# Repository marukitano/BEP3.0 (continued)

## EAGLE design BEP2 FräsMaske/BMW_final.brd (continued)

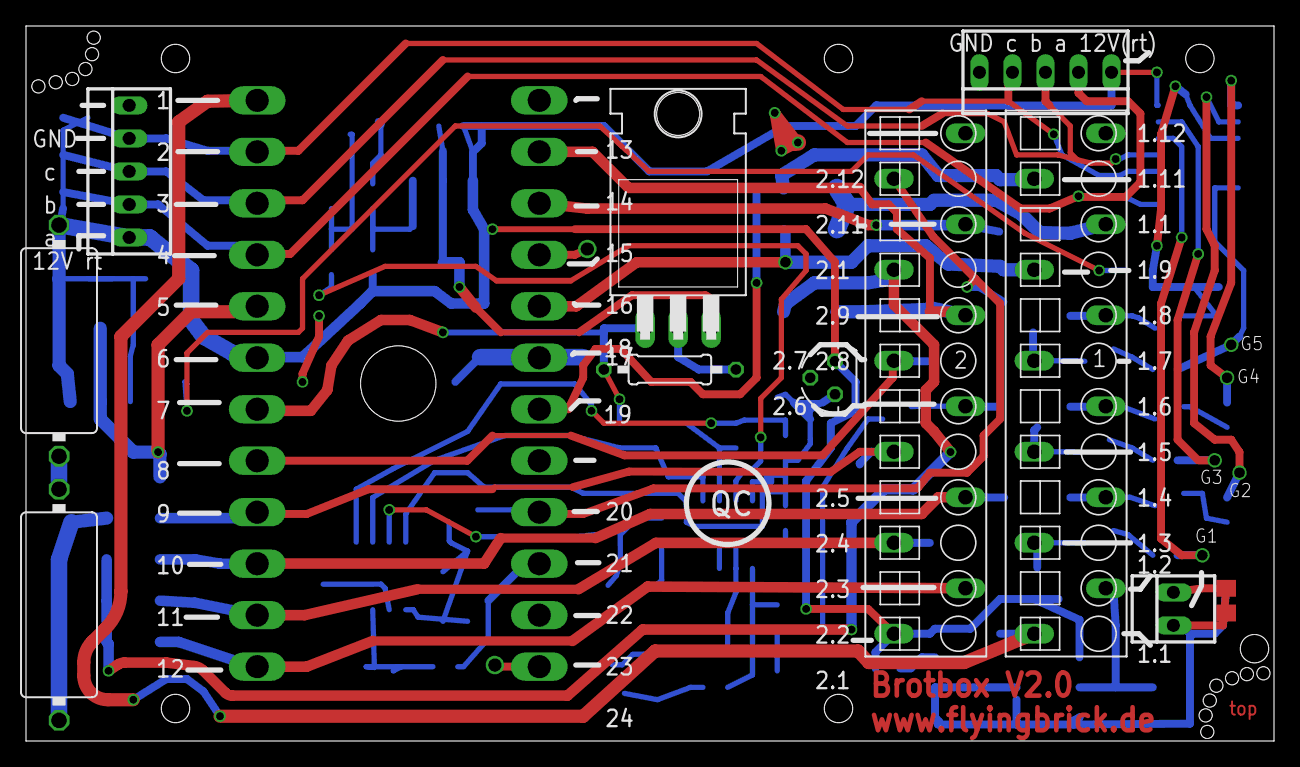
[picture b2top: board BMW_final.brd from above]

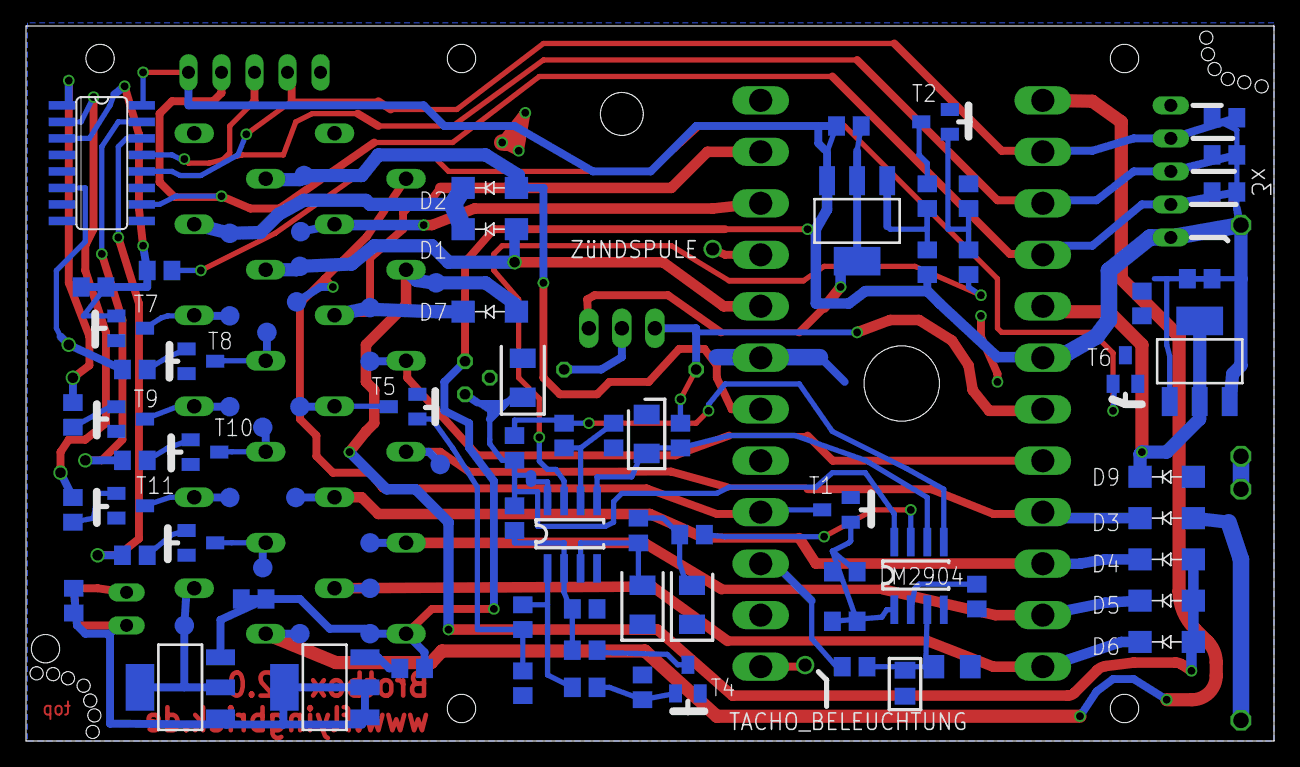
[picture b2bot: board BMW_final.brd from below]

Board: 2 copper layers, 96.0 x 55.0 mm, 105 parts (93 on the bottom side), 73 nets.

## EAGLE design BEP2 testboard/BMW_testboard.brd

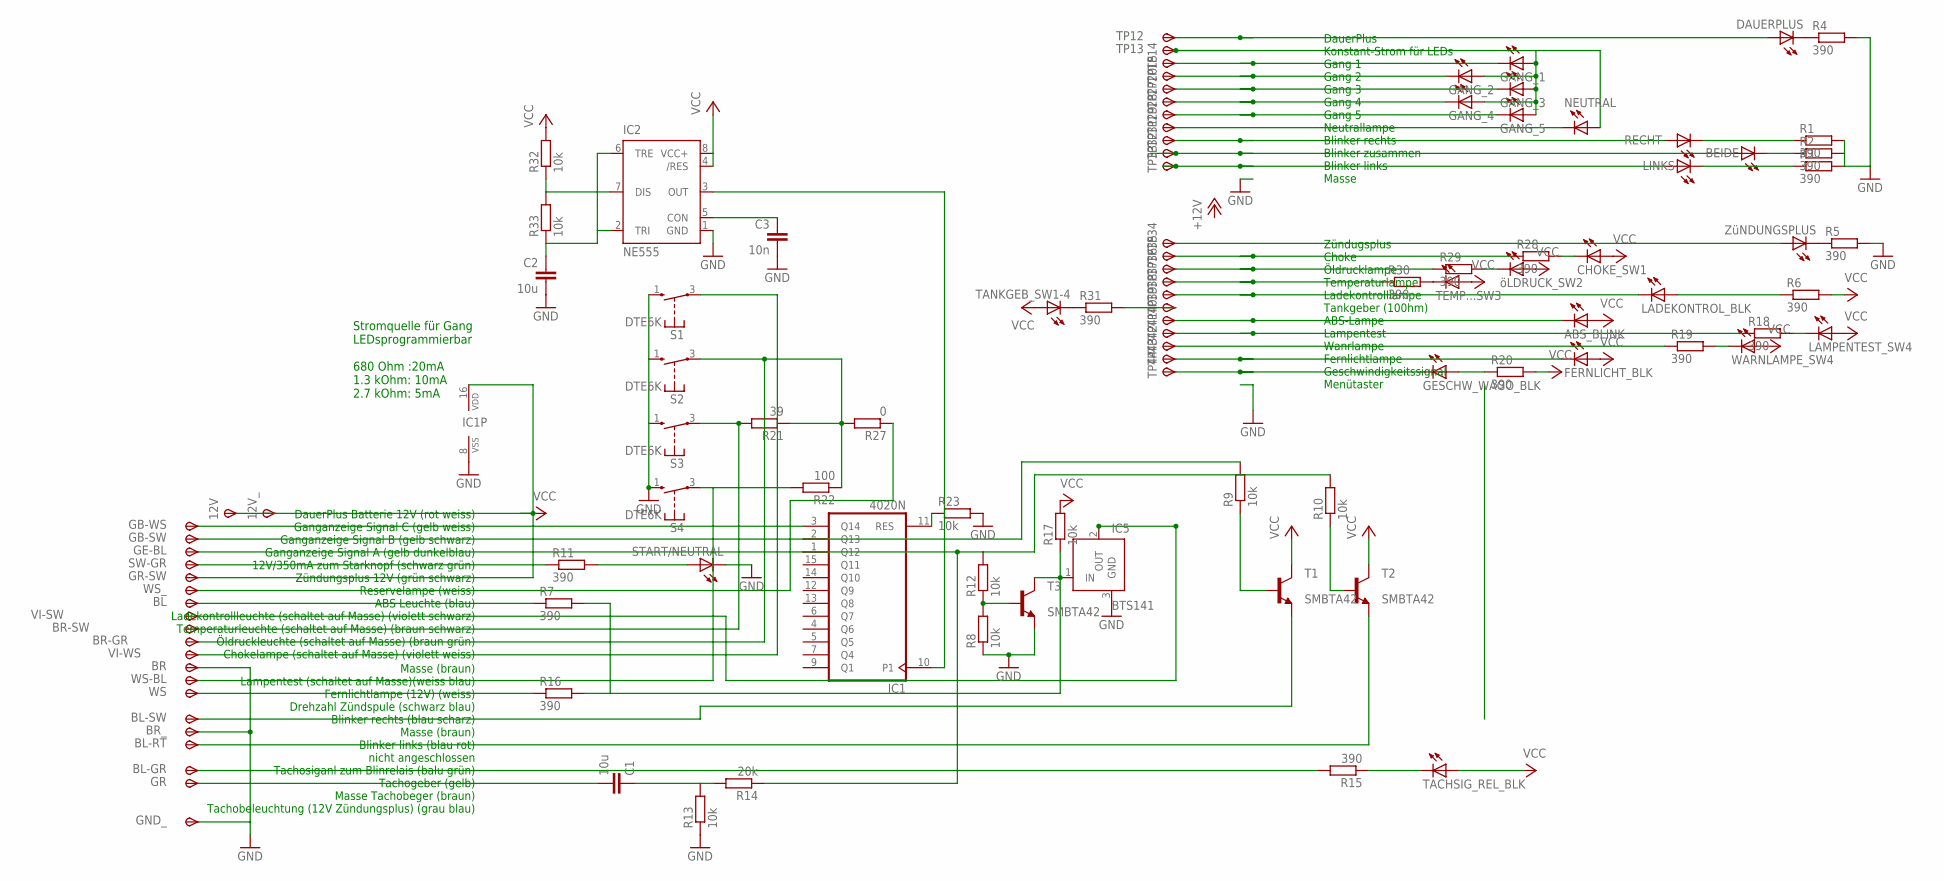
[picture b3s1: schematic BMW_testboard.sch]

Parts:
12V, 12V_: TPSPAD1-1.5MM; P1-13
ABS_BLINK: TLLY4400; LED3MM
BEIDE: TLLY4400; LED3MM
BL: TPSPAD1-1.5MM; P1-13
BL-GR: TPSPAD1-1.5MM; P1-13
BL-RT: TPSPAD1-1.5MM; P1-13
BL-SW: TPSPAD1-1.5MM; P1-13
BR: TPSPAD1-1.5MM; P1-13
BR-GR: TPSPAD1-1.5MM; P1-13
BR-SW: TPSPAD1-1.5MM; P1-13
BR_: TPSPAD1-1.5MM; P1-13
C1, C2: 10u; C025-024X044
C3: 10n; C025-024X044
CHOKE_SW1: TLLY4400; LED3MM
DAUERPLUS: TLLY4400; LED3MM
FERNLICHT_BLK: TLLY4400; LED3MM
GANG_1, GANG_2, GANG_3, GANG_4, GANG_5: TLLY4400; LED3MM
GB-SW: TPSPAD1-1.5MM; P1-13
GB-WS: TPSPAD1-1.5MM; P1-13
GE-BL: TPSPAD1-1.5MM; P1-13
GESCHW_WAGO_BLK: TLLY4400; LED3MM
GND_: TPSPAD1-1.5MM; P1-13
GR: TPSPAD1-1.5MM; P1-13
GR-SW: TPSPAD1-1.5MM; P1-13
IC1: 4020N; DIL16
IC2: NE555; DIL-08
IC5: BTS141; TO220-3-45
LADEKONTROL_BLK: TLLY4400; LED3MM
LAMPENTEST_SW4: TLLY4400; LED3MM
LINKS: TLLY4400; LED3MM
NEUTRAL: TLLY4400; LED3MM
R1, R2, R3, R4, R5, R6, R7, R11, R15, R16, R18, R19, R20, R28, R29, R30, R31: 390; R0805
R8, R9, R10, R12, R17, R23: 10k; R0805
R13, R32: 10k; 0207/12
R14: 20k; 0207/12
R21: 39; 0207/12
R22: 100; 0207/12
R27: 0; 0207/12
R33: 10k; 0207/15
RECHT: TLLY4400; LED3MM
S1, S2, S3, S4: DTE6K
START/NEUTRAL: TLLY4400; LED3MM
SW-GR: TPSPAD1-1.5MM; P1-13
T1, T2, T3: MMBTA42LT1-NPN-SOT23-BEC; SOT23-BEC
TACHSIG_REL_BLK: TLLY4400; LED3MM
TANKGEB_SW1-4: TLLY4400; LED3MM
TEMP...SW3: TLLY4400; LED3MM
TP12, TP13, TP14, TP15, TP20, TP27, TP28, TP29, TP31, TP32, TP33, TP34, TP35, TP36, TP37, TP38, TP39, TP40, TP41, TP42, TP43, TP44: TPSPAD1-1.5MM; P1-13
VI-SW: TPSPAD1-1.5MM; P1-13
VI-WS: TPSPAD1-1.5MM; P1-13
WARNLAMPE_SW4: TLLY4400; LED3MM
WS: TPSPAD1-1.5MM; P1-13
WS-BL: TPSPAD1-1.5MM; P1-13
WS_: TPSPAD1-1.5MM; P1-13
ZüNDUNGSPLUS: TLLY4400; LED3MM
öLDRUCK_SW2: TLLY4400; LED3MM

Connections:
GND: BR.TP, BR_.TP, C2.2, C3.2, GND_.TP, IC1.8 (VSS), IC2.1 (GND), IC5.3 (GND), R1.2, R2.2, R3.2, R4.2, R5.2, R8.1, R13.1, R23.2, S1.1 (S), S2.1 (S), S3.1 (S), S4.1 (S), START/NEUTRAL.K (C), T3.E
unnamed: R19.1, TP42.TP
unnamed: R31.2, TP39.TP
unnamed: GB-WS.TP, IC1.3 (Q14)
unnamed: ABS_BLINK.K (C), TP40.TP
unnamed: GB-SW.TP, IC1.2 (Q13), R9.2
unnamed: TP34.TP, ZüNDUNGSPLUS.A
unnamed: IC1.11 (RES), R23.1
unnamed: R30.2, TEMP...SW3.K (C)
unnamed: R29.1, TP36.TP
unnamed: R30.1, TP37.TP
unnamed: R19.2, WARNLAMPE_SW4.K (C)
unnamed: R11.2, START/NEUTRAL.A
unnamed: R18.1, TP41.TP
unnamed: RECHT.A, TP31.TP
unnamed: LINKS.A, TP33.TP
unnamed: BEIDE.A, TP32.TP
unnamed: R11.1, SW-GR.TP
unnamed: LAMPENTEST_SW4.K (C), R18.2
unnamed: LADEKONTROL_BLK.A, R6.1
unnamed: GESCHW_WAGO_BLK.K (C), TP44.TP
unnamed: R1.1, RECHT.K (C)
unnamed: BEIDE.K (C), R2.1
unnamed: LINKS.K (C), R3.1
unnamed: DAUERPLUS.K (C), R4.1
unnamed: GESCHW_WAGO_BLK.A, R20.1
unnamed: DAUERPLUS.A, TP12.TP
unnamed: R5.1, ZüNDUNGSPLUS.K (C)
unnamed: FERNLICHT_BLK.K (C), TP43.TP
unnamed: BL.TP, R7.1
unnamed: IC5.2 (OUT), VI-SW.TP
unnamed: R22.2, S4.3, WS-BL.TP
unnamed: BR-GR.TP, R21.1, R22.1, R27.2, S2.3
unnamed: R9.1, T1.B
unnamed: R10.1, T2.B
unnamed: BL-SW.TP, T1.E
unnamed: BL-RT.TP, T2.E
unnamed: R8.2, R12.1, T3.B
unnamed: C1.2, GR.TP
unnamed: C1.1, R13.2, R14.2
unnamed: GE-BL.TP, IC1.1 (Q12), R10.2, R12.2, R14.1
unnamed: R15.1, TACHSIG_REL_BLK.K (C)
unnamed: BL-GR.TP, R15.2
unnamed: NEUTRAL.K (C), TP29.TP
unnamed: R16.1, WS.TP
unnamed: R28.1, TP35.TP
unnamed: IC5.1 (IN), R7.2, R16.2, R17.1, T3.C
unnamed: BR-SW.TP, R21.2, S3.3
unnamed: GANG_1.A, GANG_2.A, GANG_3.A, GANG_4.A, GANG_5.A, NEUTRAL.A, TP13.TP
unnamed: R29.2, öLDRUCK_SW2.K (C)
unnamed: CHOKE_SW1.K (C), R28.2
unnamed: GANG_5.K (C), TP28.TP
unnamed: R31.1, TANKGEB_SW1-4.K (C)
unnamed: C2.1, IC2.2 (TRI), IC2.6 (TRE), R33.1
unnamed: IC1.10 (P1), IC2.3 (OUT)
unnamed: IC2.7 (DIS), R32.1, R33.2
unnamed: C3.1, IC2.5 (CON)
unnamed: GANG_3.K (C), TP20.TP
unnamed: GANG_4.K (C), TP27.TP
unnamed: GANG_2.K (C), TP15.TP
unnamed: GANG_1.K (C), TP14.TP
unnamed: LADEKONTROL_BLK.K (C), TP38.TP
VCC: 12V.TP, 12V_.TP, ABS_BLINK.A, CHOKE_SW1.A, FERNLICHT_BLK.A, GR-SW.TP, IC1.16 (VDD), IC2.4 (/RES), IC2.8 (VCC+), LAMPENTEST_SW4.A, R6.2, R17.2, R20.2, R32.2, T1.C, T2.C, TACHSIG_REL_BLK.A, TANKGEB_SW1-4.A, TEMP...SW3.A, WARNLAMPE_SW4.A, öLDRUCK_SW2.A
VI-WS: S1.3, VI-WS.TP
WS: R27.1, WS_.TP

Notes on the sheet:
Zündugsplus Choke Öldrucklampe Temperaturlampe Ladekontrolllampe Tankgeber (100hm) ABS-Lampe Lampentest Wanrlampe Fernlichtlampe Geschwindigkeitssignal Menütaster
DauerPlus Konstant-Strom für LEDs Gang 1 Gang 2 Gang 3 Gang 4 Gang 5 Neutrallampe Blinker rechts Blinker zusammen Blinker links Masse
DauerPlus Batterie 12V (rot weiss) Ganganzeige Signal C (gelb weiss) Ganganzeige Signal B (gelb schwarz) Ganganzeige Signal A (gelb dunkelblau) 12V/350mA zum Starknopf (schwarz grün) Zündungsplus 12V (grün schwarz) Reservelampe (weiss) ABS Leuchte (blau) Ladekontrollleuchte (schaltet auf Masse) (vi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
Masse (braun) Lampentest (schaltet auf Masse)(weiss blau) Fernlichtlampe (12V) (weiss) Drehzahl Zündspule (schwarz blau) Blinker rechts (blau scharz) Masse (braun) Blinker links (blau rot) nicht angeschlossen Tachosiganl zum Blinrelais (balu grün) Tachogeber (gelb) Masse Tachobeger (braun) Tachobel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
Stromquelle für Gang LEDsprogrammierbar 680 Ohm :20mA 1.3 kOhm: 10mA 2.7 kOhm: 5mA

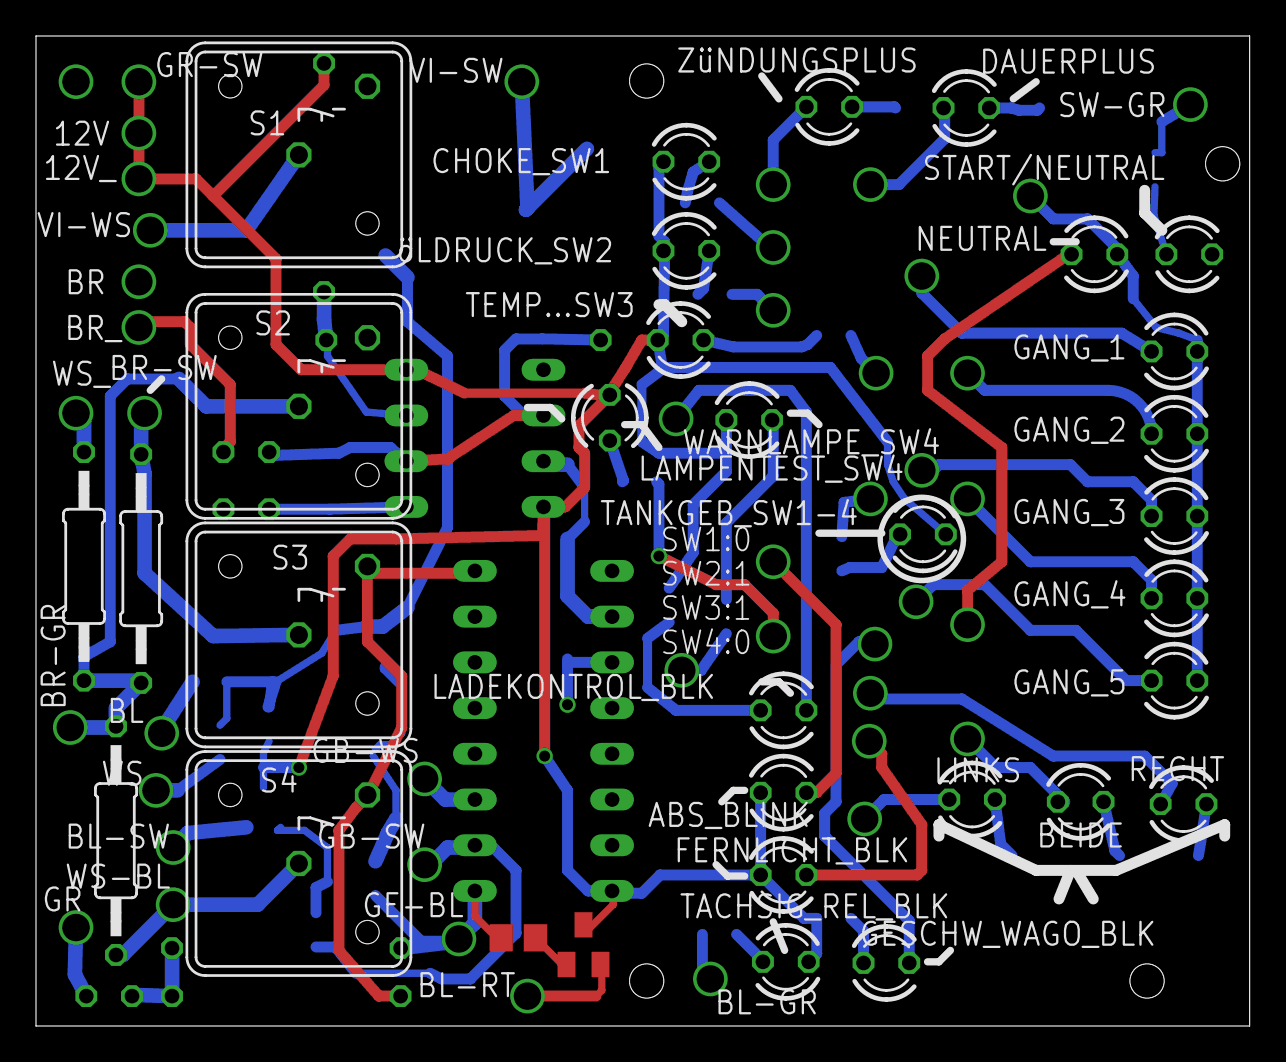
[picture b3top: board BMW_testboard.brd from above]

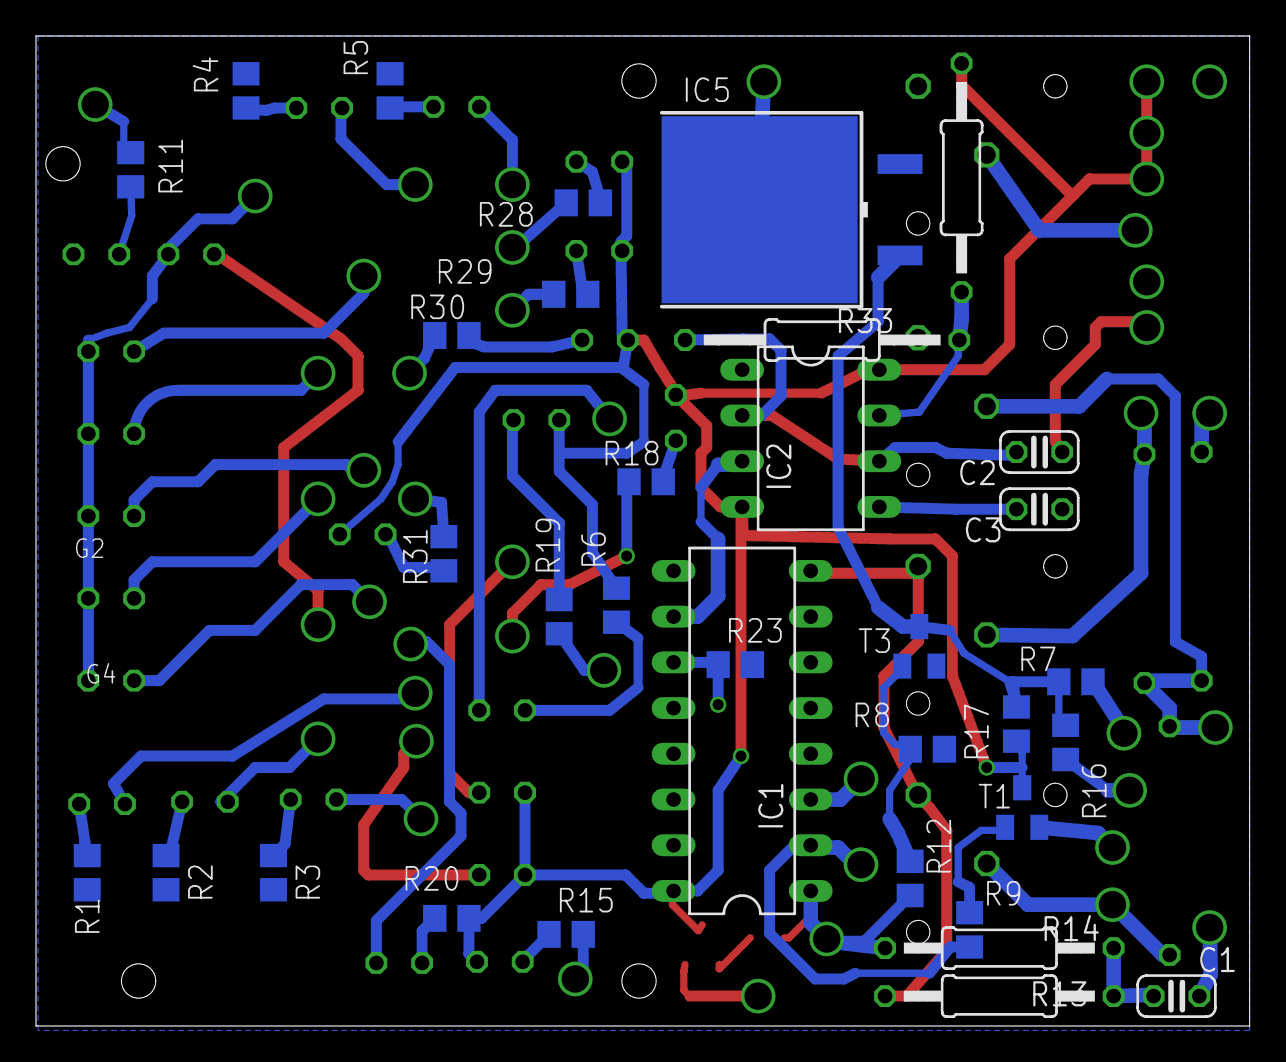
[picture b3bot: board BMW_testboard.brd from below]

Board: 2 copper layers, 67.4 x 55.0 mm, 110 parts (56 on the bottom side), 65 nets.

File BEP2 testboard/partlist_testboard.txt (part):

Partlist

Exported from BMW_testboard.sch at 27.07.2015 17:11:16

EAGLE Version 6.4.0 Copyright (c) 1988-2013 CadSoft

Assembly variant: 

Part            Value          Device                   Package      Library             Sheet

öLDRUCK_SW2     TLLY4400       TLLY4400                 LED3MM       led                 1
12V             TPSPAD1-1.5MM  TPSPAD1-1.5MM            P1-13        testpin_BMW         1
12V_            TPSPAD1-1.5MM  TPSPAD1-1.5MM            P1-13        testpin_BMW         1
ABS_BLINK       TLLY4400       TLLY4400                 LED3MM       led                 1
BEIDE           TLLY4400       TLLY4400                 LED3MM       led                 1
BL              TPSPAD1-1.5MM  TPSPAD1-1.5MM            P1-13        testpin_BMW         1
BL-GR           TPSPAD1-1.5MM  TPSPAD1-1.5MM            P1-13        testpin_BMW         1
BL-RT           TPSPAD1-1.5MM  TPSPAD1-1.5MM            P1-13        testpin_BMW         1
BL-SW           TPSPAD1-1.5MM  TPSPAD1-1.5MM            P1-13        testpin_BMW         1
BR              TPSPAD1-1.5MM  TPSPAD1-1.5MM            P1-13        testpin_BMW         1
BR-GR           TPSPAD1-1.5MM  TPSPAD1-1.5MM            P1-13        testpin_BMW         1
BR-SW           TPSPAD1-1.5MM  TPSPAD1-1.5MM            P1-13        testpin_BMW         1
BR_             TPSPAD1-1.5MM  TPSPAD1-1.5MM            P1-13        testpin_BMW         1
C1              10u            C-EU025-024X044          C025-024X044 rcl                 1
C2              10u            C-EU025-024X044          C025-024X044 rcl                 1
C3              10n            C-EU025-024X044          C025-024X044 rcl                 1
CHOKE_SW1       TLLY4400       TLLY4400                 LED3MM       led                 1
DAUERPLUS       TLLY4400       TLLY4400                 LED3MM       led                 1
FERNLICHT_BLK   TLLY4400       TLLY4400                 LED3MM       led                 1
GANG_1          TLLY4400       TLLY4400                 LED3MM       led                 1
GANG_2          TLLY4400       TLLY4400                 LED3MM       led                 1
GANG_3          TLLY4400       TLLY4400                 LED3MM       led                 1
GANG_4          TLLY4400       TLLY4400                 LED3MM       led                 1
GANG_5          TLLY4400       TLLY4400                 LED3MM       led                 1
GB-SW           TPSPAD1-1.5MM  TPSPAD1-1.5MM            P1-13        testpin_BMW         1
GB-WS           TPSPAD1-1.5MM  TPSPAD1-1.5MM            P1-13        testpin_BMW         1
GE-BL           TPSPAD1-1.5MM  TPSPAD1-1.5MM            P1-13        testpin_BMW         1
GESCHW_WAGO_BLK TLLY4400       TLLY4400                 LED3MM       led                 1
GND_            TPSPAD1-1.5MM  TPSPAD1-1.5MM            P1-13        testpin_BMW         1
GR              TPSPAD1-1.5MM  TPSPAD1-1.5MM            P1-13        testpin_BMW         1
GR-SW           TPSPAD1-1.5MM  TPSPAD1-1.5MM            P1-13        testpin_BMW         1
IC1             4020N          4020N                    DIL16        40xx                1
IC2             NE555          NE555                    DIL-08       st-microelectronics 1
IC5             BTS141         BTS141                   TO220-3-45   optosonde_bruker    1
LADEKONTROL_BLK TLLY4400       TLLY4400                 LED3MM       led                 1
LAMPENTEST_SW4  TLLY4400       TLLY4400                 LED3MM       led                 1
LINKS           TLLY4400       TLLY4400                 LED3MM       led                 1
NEUTRAL         TLLY4400       TLLY4400                 LED3MM       led                 1
R1              390            R-EU_R0805               R0805        rcl                 1
R2              390            R-EU_R0805               R0805        rcl                 1
R3              390            R-EU_R0805               R0805        rcl                 1
R4              390            R-EU_R0805               R0805        rcl                 1
R5              390            R-EU_R0805               R0805        rcl                 1
R6              390            R-EU_R0805               R0805        rcl                 1
R7              390            R-EU_R0805               R0805        rcl                 1
R8              10k            R-EU_R0805               R0805        rcl                 1
R9              10k            R-EU_R0805               R0805        rcl                 1
R10             10k            R-EU_R0805               R0805        rcl                 1
R11             390            R-EU_R0805               R0805        rcl                 1
R12             10k            R-EU_R0805               R0805        rcl                 1
R13             10k            R-EU_0207/12             0207/12      rcl                 1
R14             20k            R-EU_0207/12             0207/12      rcl                 1
R15             390            R-EU_R0805               R0805        rcl                 1
R16             390            R-EU_R0805               R0805        rcl                 1
R17             10k            R-EU_R0805               R0805        rcl                 1
R18             390            R-EU_R0805               R0805        rcl                 1
R19             390            R-EU_R0805               R0805        rcl                 1
R20             390            R-EU_R0805               R0805        rcl                 1
R21             39             R-EU_0207/12             0207/12      rcl                 1
R22             100            R-EU_0207/12             0207/12      rcl                 1
R23             10k            R-EU_R0805               R0805        rcl                 1
R27             0              R-EU_0207/12             0207/12      rcl                 1
R28             390            R-EU_R0805               R0805        rcl                 1
R29             390            R-EU_R0805               R0805        rcl                 1
R30             390            R-EU_R0805               R0805        rcl                 1
R31             390            R-EU_R0805               R0805        rcl                 1
R32             10k            R-EU_0207/12             0207/12      rcl                 1
R33             10k            R-EU_0207/15             0207/15      rcl                 1
RECHT           TLLY4400       TLLY4400                 LED3MM       led                 1
S1              DTE6K          DTE6K                    DTE6K        switch              1
S2              DTE6K          DTE6K                    DTE6K        switch              1
S3              DTE6K          DTE6K                    DTE6K        switch              1
S4              DTE6K          DTE6K                    DTE6K        switch              1
START/NEUTRAL   TLLY4400       TLLY4400                 LED3MM       led                 1
SW-GR           TPSPAD1-1.5MM  TPSPAD1-1.5MM            P1-13        testpin_BMW         1
T1                             MMBTA42LT1-NPN-SOT23-BEC SOT23-BEC    transistor          1
T2                             MMBTA42LT1-NPN-SOT23-BEC SOT23-BEC    transistor          1
T3                             MMBTA42LT1-NPN-SOT23-BEC SOT23-BEC    transistor          1
TACHSIG_REL_BLK TLLY4400       TLLY4400                 LED3MM       led                 1
TANKGEB_SW1-4   TLLY4400       TLLY4400                 LED3MM       led                 1
TEMP...SW3      TLLY4400       TLLY4400                 LED3MM       led                 1
TP12            TPSPAD1-1.5MM  TPSPAD1-1.5MM            P1-13        testpin_BMW         1
TP13            TPSPAD1-1.5MM  TPSPAD1-1.5MM            P1-13        testpin_BMW         1
TP14            TPSPAD1-1.5MM  TPSPAD1-1.5MM            P1-13        testpin_BMW         1
TP15            TPSPAD1-1.5MM  TPSPAD1-1.5MM            P1-13        testpin_BMW         1
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
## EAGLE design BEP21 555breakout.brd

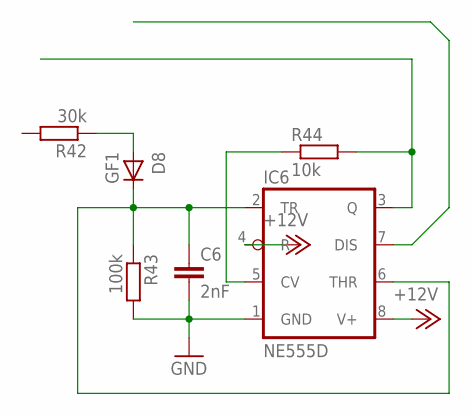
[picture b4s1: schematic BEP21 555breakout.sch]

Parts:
C6: 2nF; C1206K
D8: GF1; SMA-DO214AC
IC6: NE555D; SO08
R42: 30k; R0805
R43: 100k; R0805
R44: 10k; R0805

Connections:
+12V: IC6.4 (R), IC6.8 (V+)
GND: C6.2, IC6.1 (GND), R43.2
unnamed: D8.A, R42.1
unnamed: IC6.3 (Q), R44.2
unnamed: IC6.5 (CV), R44.1
unnamed: C6.1, D8.K (C), IC6.2 (TR), IC6.6 (THR), R43.1

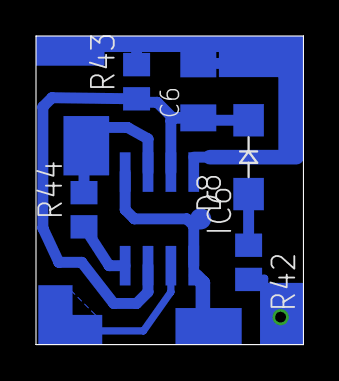
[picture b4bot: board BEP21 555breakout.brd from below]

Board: 2 copper layers, 14.9 x 17.1 mm, 6 parts (6 on the bottom side), 6 nets.
